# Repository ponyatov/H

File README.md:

# ALYEH platform
## ALYEH:Hardware
Библиотека универсальных электронных модулей

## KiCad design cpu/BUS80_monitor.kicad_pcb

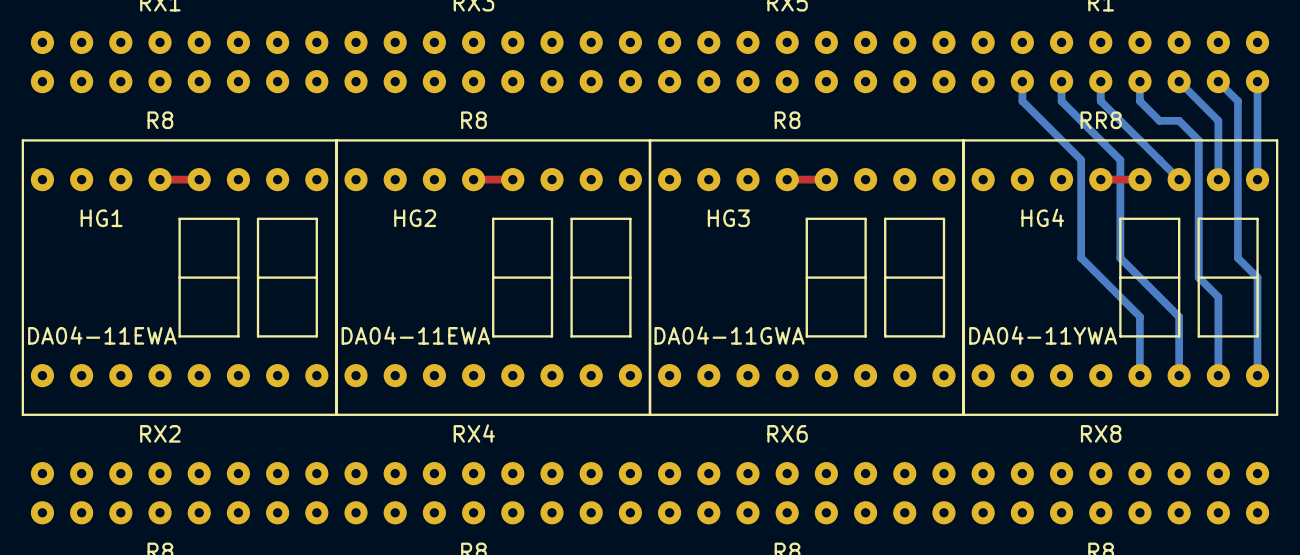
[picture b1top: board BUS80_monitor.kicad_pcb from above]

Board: 2 copper layers, 12 parts (0 on the bottom side), 50 nets.

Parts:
HG1, HG2: DA04-11EWA; DA04-11xWA
HG3: DA04-11GWA; DA04-11xWA
HG4: DA04-11YWA; DA04-11xWA
R1: RR8; R8_THRU
RX1, RX2, RX3, RX4, RX5, RX6, RX8: R8; R8_THRU

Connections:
/VCC5: HG1.4, HG1.5, HG2.4, HG2.5, HG3.4, HG3.5, HG4.4, HG4.5
/hg4a1: HG4.15, R1.13
/hg4b1: HG4.13, R1.10
/hg4c1: HG4.1, R1.16
/hg4d1: HG4.3, R1.12
/hg4e1: HG4.2, R1.14
/hg4f1: HG4.14, R1.11
/hg4g1: HG4.16, R1.15
unnamed: HG3.15, RX5.16
unnamed: HG1.16, RX1.10
unnamed: HG1.14, RX1.11
unnamed: HG1.2, RX1.12
unnamed: HG1.3, RX1.13
unnamed: HG1.1, RX1.14
unnamed: HG1.13, RX1.15
unnamed: HG1.15, RX1.16
unnamed: HG1.10, RX2.1
unnamed: HG3.13, RX5.15
unnamed: HG3.1, RX5.14
unnamed: HG3.3, RX5.13
unnamed: HG3.2, RX5.12
unnamed: HG3.14, RX5.11
unnamed: HG3.16, RX5.10
unnamed: HG2.15, RX3.16
unnamed: HG2.10, RX4.1, RX8.5
unnamed: HG2.16, RX3.10
unnamed: HG2.14, RX3.11
unnamed: HG2.2, RX3.12
unnamed: HG2.3, RX3.13
unnamed: HG2.1, RX3.14
unnamed: HG2.13, RX3.15, RX8.7
unnamed: HG1.9, RX2.7, RX8.4
unnamed: HG1.11, RX2.6, RX8.3
unnamed: HG1.7, RX2.5, RX8.2
unnamed: HG1.6, RX2.4, RX8.1
unnamed: HG1.8, RX2.3
unnamed: HG1.12, RX2.2
unnamed: HG2.11, RX4.6
unnamed: HG2.7, RX4.5
unnamed: HG2.6, RX4.4
unnamed: HG2.8, RX4.3
unnamed: HG2.12, RX4.2
unnamed: HG2.9, RX4.7
unnamed: HG3.9, RX6.7
unnamed: HG3.11, RX6.6
unnamed: HG3.7, RX6.5
unnamed: HG3.6, RX6.4
unnamed: HG3.8, RX6.3
unnamed: HG3.12, RX6.2
unnamed: HG3.10, RX6.1

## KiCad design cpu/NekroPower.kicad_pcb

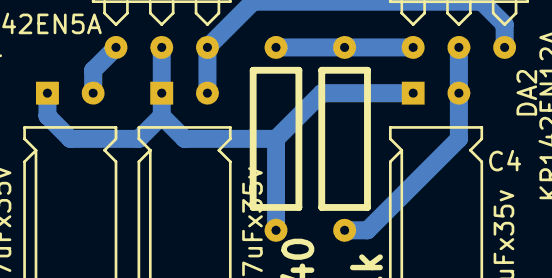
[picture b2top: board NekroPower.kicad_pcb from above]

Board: 2 copper layers, 7 parts (0 on the bottom side), 5 nets.

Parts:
C1, C2, C4: 47uFx35v; CP_5x9_H
DA1: KR142EN5A; TO-220_H
DA2: KR142EN12A; TO-220_H
R1: R40; TH_2_RH_1W4
R2: 1k; TH_2_RH_1W4

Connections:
0: C1.1, C2.1, C4.1, DA1.2, R1.1
unnamed: C1.2, DA1.1
unnamed: C2.2, DA1.3, DA2.3
unnamed: DA2.1, R1.2, R2.1
unnamed: C4.2, DA2.2, R2.2

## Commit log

2015-04-09 + kicad lib + main .tex + usb + SparkFun/HEX FT232R breakout
2015-04-09 +lib/Atmel +lib/FTDI +lib/STMicro +module usb/HEX_FT232RL +odurino.sch for tests
2015-04-09 +.igitignore
2015-04-09 + odurino.brd pcb + HEX_FT232 element graphics
2015-05-10 + tex project
2015-05-10 +/tmp
2015-05-10 + FT2232H
2015-06-11 + interface/RS232_5v
2015-06-11 + doc/
2015-06-11 * RS232_5v - tex
2015-06-11 * RS232_5v sch svg fix
2015-06-11 + lib/TVS supressors
2015-06-11 + TVS2 supressors on TTL lines
2015-06-13 * lib/YVS/TVD2
2015-06-13 - texlipse
2015-06-13 + RS232_5v board
2015-06-13 + lib/SMD THRU
2015-06-13 * RS232_5v
2015-06-15 * README
2015-06-15 *README
2015-06-15 +H.tex
2015-06-15 + usb/FT* schemes
2015-06-15 - HEXFT232RL.png
2015-06-15 +CAN
2015-06-15 + CAN, SD, lib descriptions
2015-06-16 + /datasheets
2015-06-16 + LDO + TL494*
2015-06-16 +amp +cpu *power
2015-06-16 +radio
2015-06-16 *radio
2015-06-16 + TL494VIC
2015-06-16 +uSD +MEGA32
2015-06-18 +Sdinit.png
2015-07-02 + FPGA/BIN2HEX_LED
2015-07-07 +Nekrosha
2015-07-07 * cpu/Nekrosha main + cpu/BUS80_monitor + lib/LED: DA04-11xWA 2x 7LED block
2015-07-07 * DA04-11xWA: + dot pin * bus80_mon: set color letter in 7LEDs value field
2015-07-07 + lib/R comments (ru)
2015-07-07 + LED res blocks
2015-07-07 + lib/LED.mod (pcb pads) * lib/LED.lib * DA04-11xWA pin numbers
2015-07-07 * lib/LED to .pretty format
2015-07-07 + DA04-11xWA pad
2015-07-07 * legacy only libs: LED + pads R8_THRU + BUS80_MOD pad sets + ignore *bak
2015-07-08 + NekroPower + lib/ LM7805 KR142EN5A KR142EN12A
2015-07-09 + NekroPower pcb
